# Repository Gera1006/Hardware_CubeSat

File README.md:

# Hardware_CubeSat
Aquí se encuentran los archivos creados para mantener un manejo más práctico de los elementos utilizados en el diseño del hardware

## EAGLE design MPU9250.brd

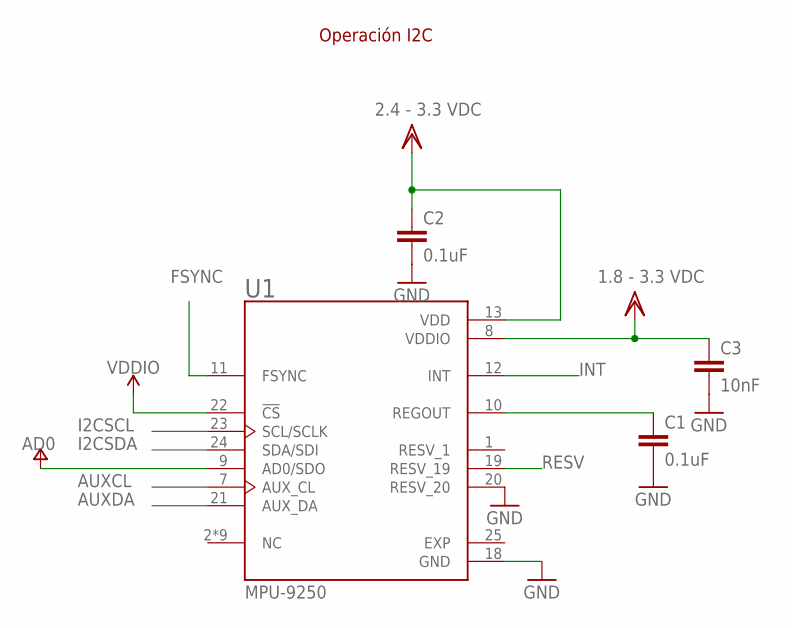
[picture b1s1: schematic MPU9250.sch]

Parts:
C1, C2: 0.1uF; 1206
C3: 10nF; 1206
U1: MPU-9250; QFN40P300X300X105-25N

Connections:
FSYNC: U1.11 (FSYNC)
GND: C1.2, C2.2, C3.2, U1.18 (GND), U1.20 (RESV_20)
INT: U1.12 (INT)
unnamed: C1.1, U1.10 (REGOUT)
RESV: U1.19 (RESV_19)
RESV_1: U1.1 (RESV_1)
V+: U1.9 (AD0/SDO)
VDD: C2.1, C3.1, U1.8 (VDDIO), U1.13 (VDD)
VDDIO: U1.22 (!CS)

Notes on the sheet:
Operación I2C

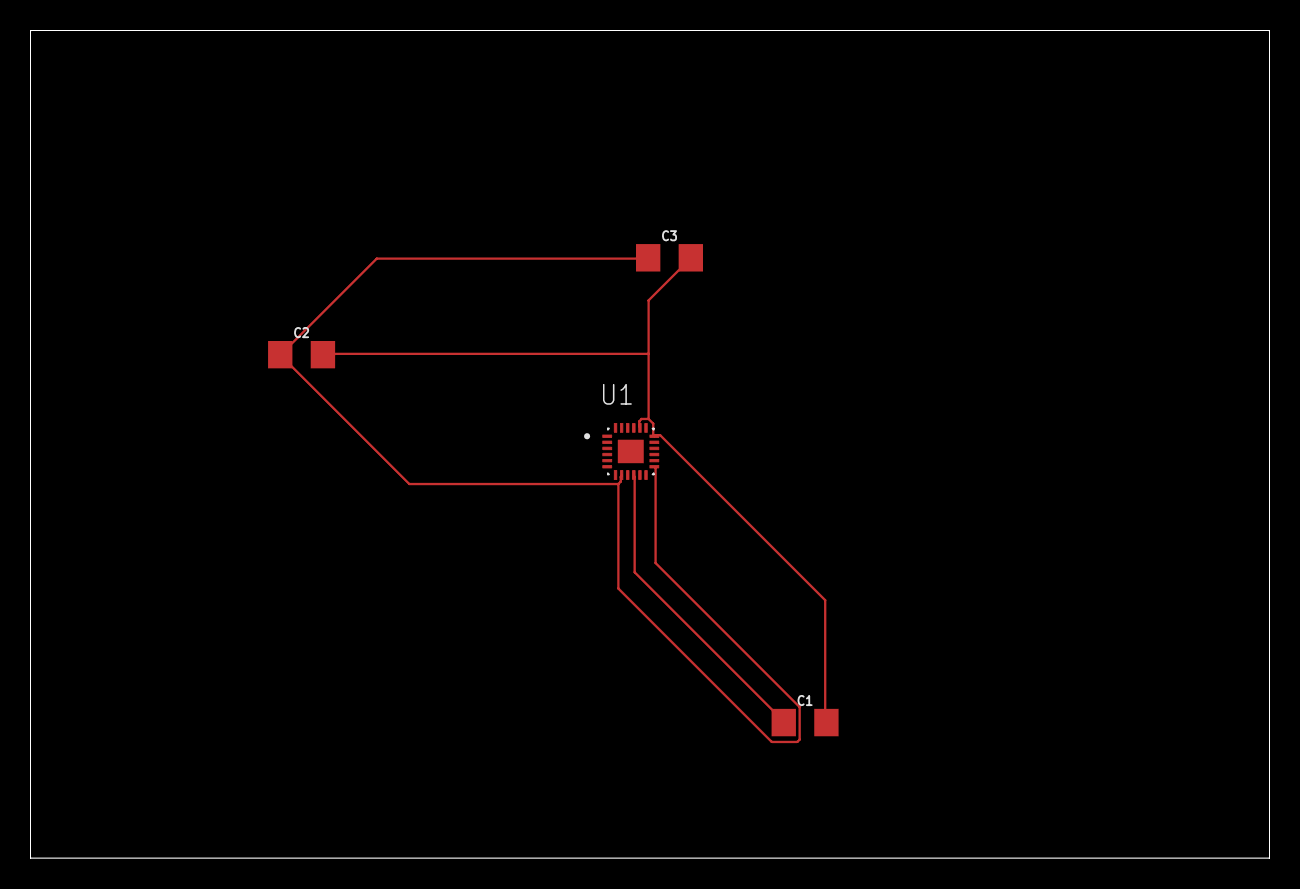
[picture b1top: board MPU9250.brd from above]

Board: 2 copper layers, 81.3 x 54.3 mm, 4 parts (0 on the bottom side), 3 nets.

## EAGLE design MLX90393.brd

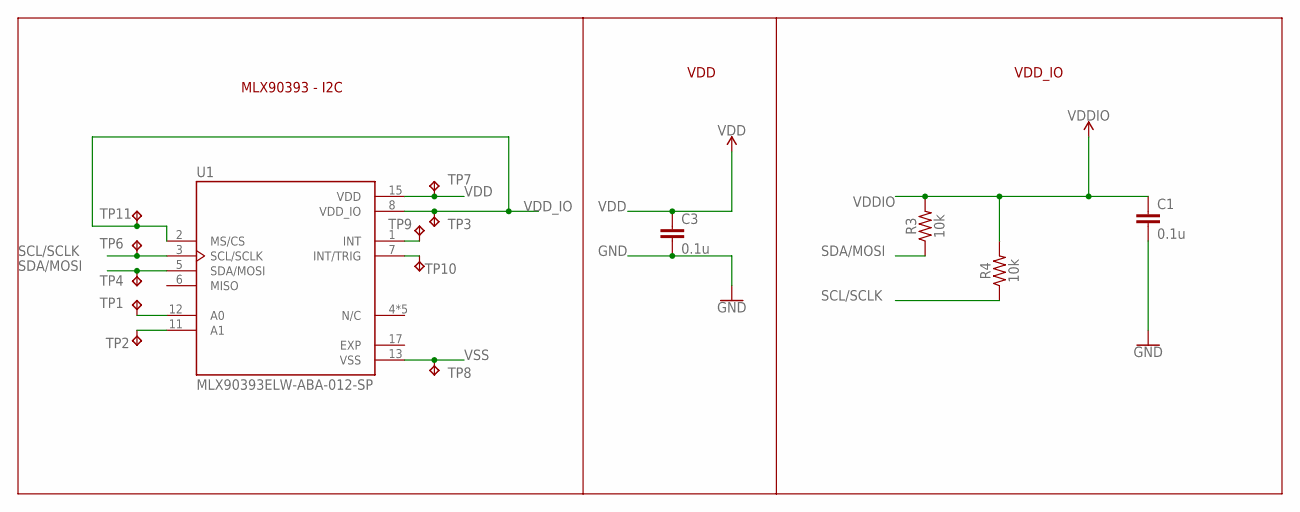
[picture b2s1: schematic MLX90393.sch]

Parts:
C1, C3: 0.1u; 1206
R3, R4: 10k; 1206
TP1, TP2, TP3, TP4, TP6, TP7, TP8, TP9, TP10, TP11: TPB1,27; B1,27
U1: MLX90393ELW-ABA-012-SP; QFN50P300X300X100-17N

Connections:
GND: C1.2, C3.2
unnamed: TP1.TP, U1.12 (A0)
unnamed: TP2.TP, U1.11 (A1)
unnamed: TP9.TP, U1.1 (INT)
unnamed: TP10.TP, U1.7 (INT/TRIG)
SCL/SCLK: R4.1, TP6.TP, U1.3 (SCL/SCLK)
SDA/MOSI: R3.1, TP4.TP, U1.5 (SDA/MOSI)
VDD: C3.1, TP7.TP, U1.15 (VDD)
VDDIO: C1.1, R3.2, R4.2
VDD_IO: TP3.TP, TP11.TP, U1.2 (MS/CS), U1.8 (VDD_IO)
VSS: TP8.TP, U1.13 (VSS)

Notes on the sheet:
MLX90393 - I2C
VDD
VDD_IO

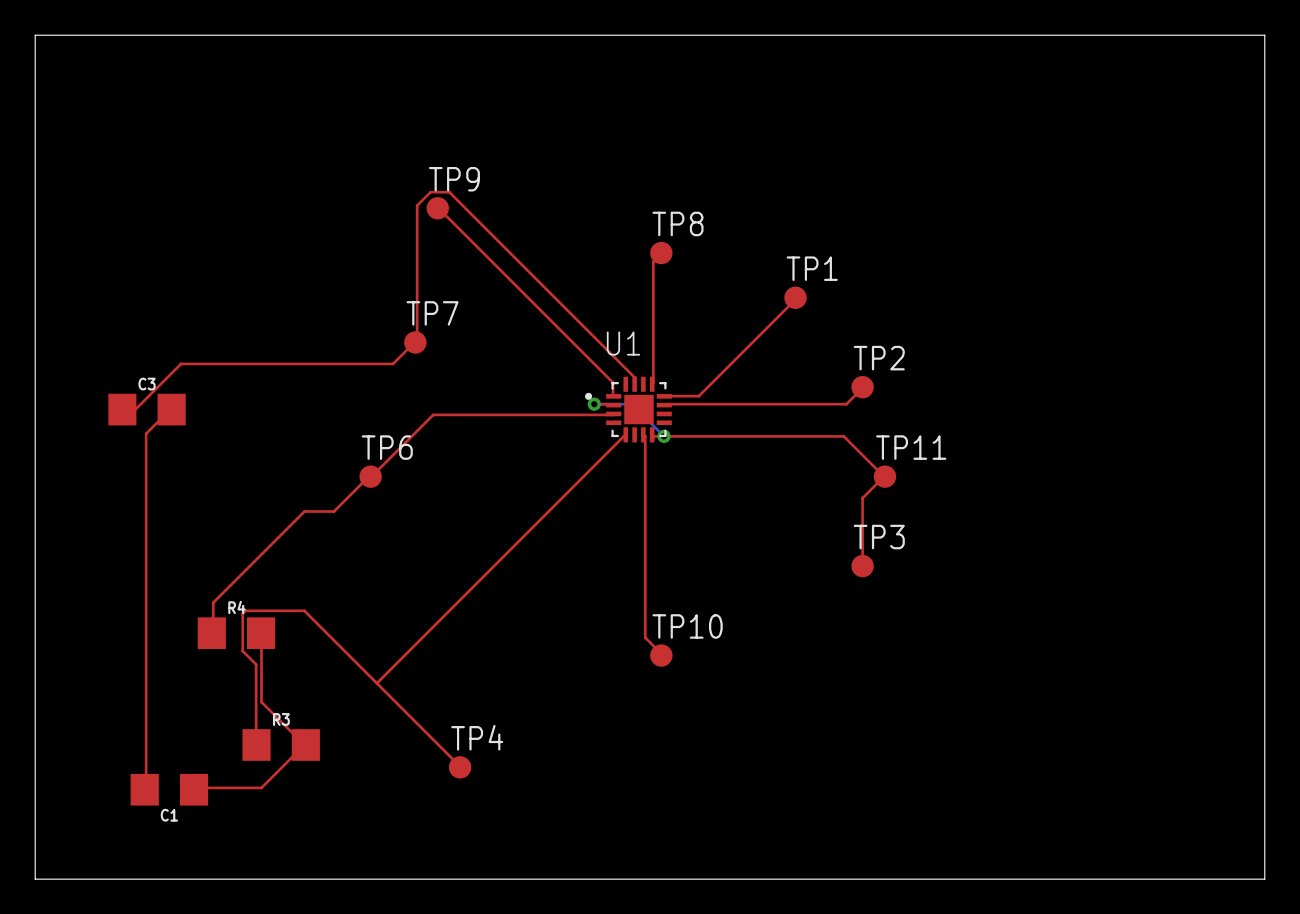
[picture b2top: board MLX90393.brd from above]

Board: 2 copper layers, 69.8 x 47.9 mm, 15 parts (0 on the bottom side), 11 nets.

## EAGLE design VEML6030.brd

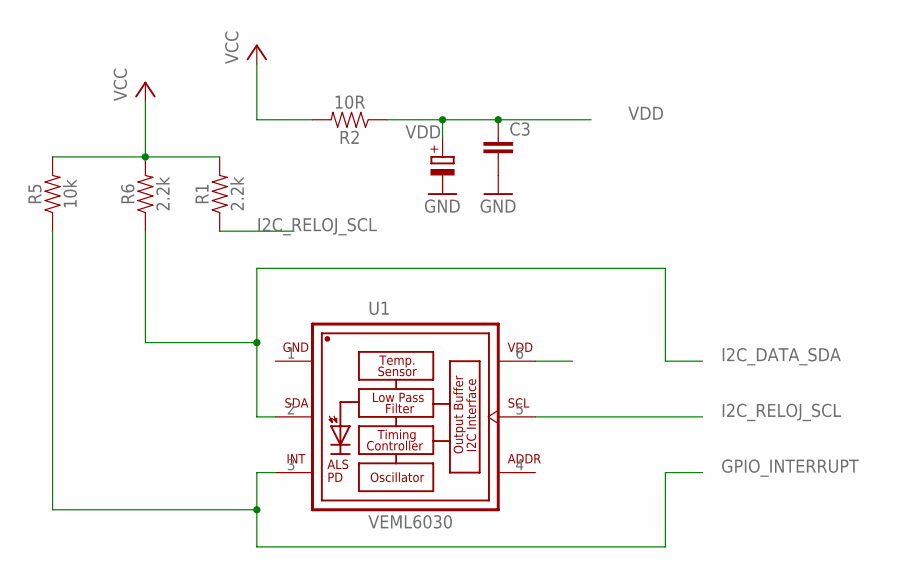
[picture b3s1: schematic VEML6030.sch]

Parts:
C3: CAP-1206; 1206
R1, R6: 2.2k; 1206
R2: 10R; 1206
R5: 10k; 1206
U1: VEML6030; VISHAY_VEML6030_2X2X0.87

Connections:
GND: C3.2, U1.1 (GND)
GPIO_INTERRUPT: R5.1, U1.3 (INT)
I2C_DATA_SDA: R6.1, U1.2 (SDA)
I2C_RELOJ_SCL: R1.1, U1.5 (SCL)
VCC: R1.2, R5.2, R6.2
VDD: C3.1, R2.1

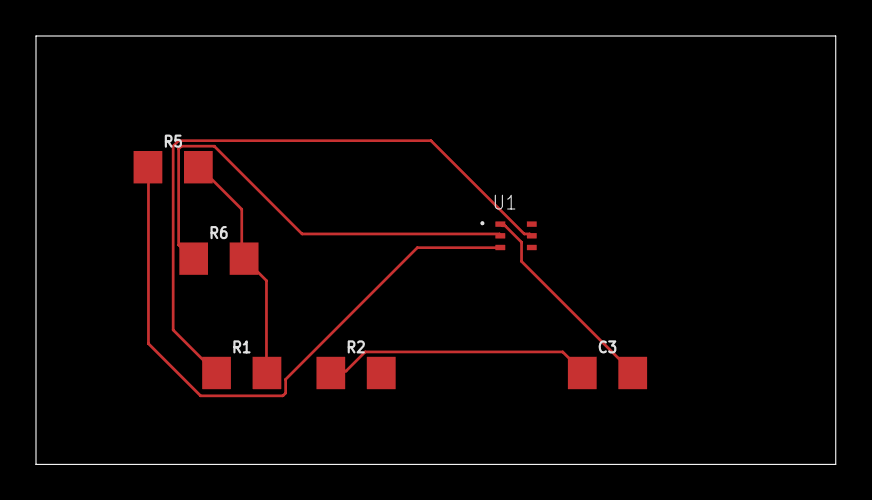
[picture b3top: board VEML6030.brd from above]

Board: 2 copper layers, 44.4 x 23.8 mm, 6 parts (0 on the bottom side), 6 nets.

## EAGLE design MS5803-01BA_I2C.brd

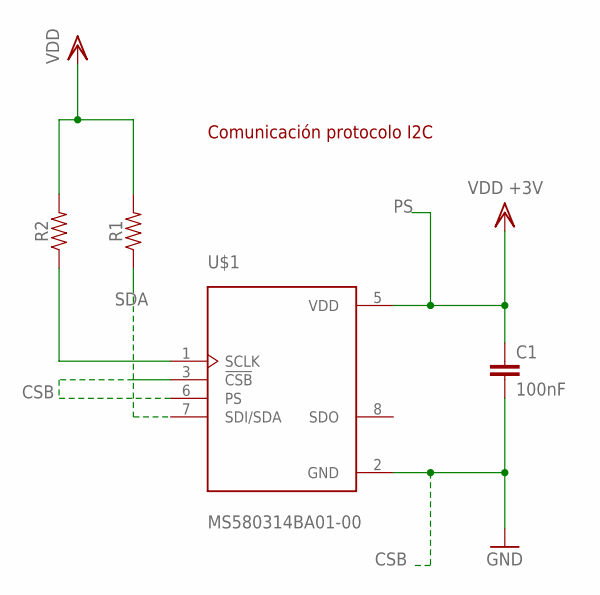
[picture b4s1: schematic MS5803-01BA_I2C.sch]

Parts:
C1: 100nF; 1206
R1, R2: 1206
U$1: MS580314BA01-00; XDCR_MS580314BA01-00

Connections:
CSB: C1.2, U$1.2 (GND), U$1.3 (!CSB), U$1.6 (PS)
PS: C1.1, U$1.5 (VDD)
SCLK: R2.1, U$1.1 (SCLK)
SDA: R1.1, U$1.7 (SDI/SDA)
VDD: R1.2, R2.2

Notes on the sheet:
Comunicación protocolo I2C

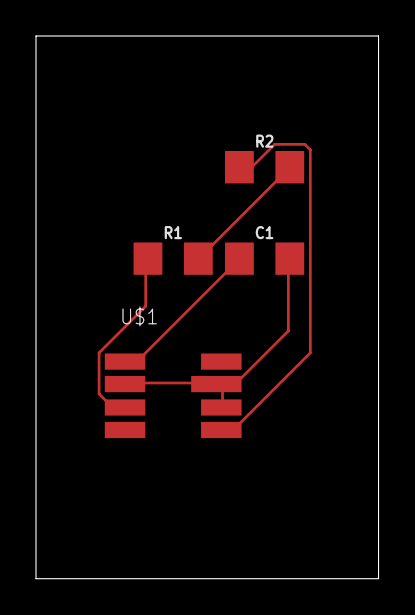
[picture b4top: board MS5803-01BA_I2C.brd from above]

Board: 2 copper layers, 19.0 x 30.1 mm, 4 parts (0 on the bottom side), 5 nets.

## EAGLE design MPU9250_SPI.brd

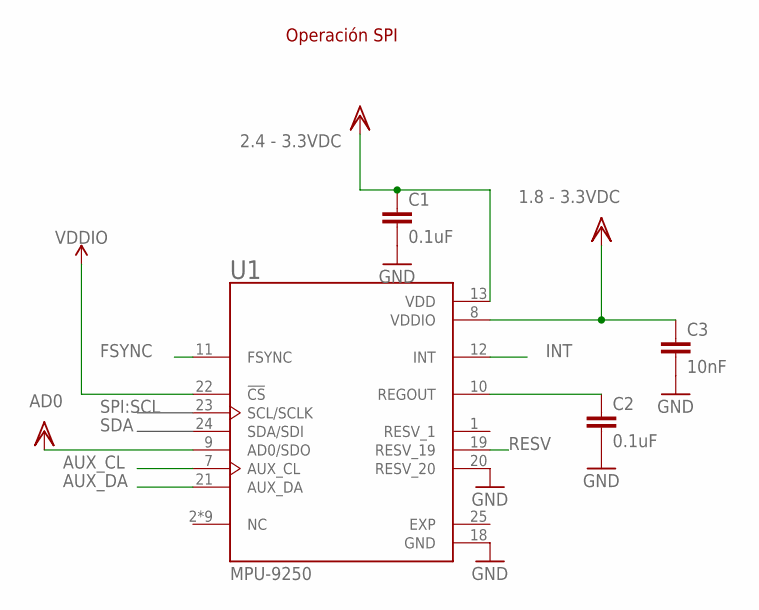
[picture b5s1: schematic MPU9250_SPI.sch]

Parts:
C1, C2: 0.1uF; 1206
C3: 10nF; 1206
U1: MPU-9250; QFN40P300X300X105-25N

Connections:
AUX_CL: U1.7 (AUX_CL)
AUX_DA: U1.21 (AUX_DA)
FSYNC: U1.11 (FSYNC)
GND: C1.2, C2.2, C3.2, U1.18 (GND), U1.20 (RESV_20)
INT: U1.12 (INT)
unnamed: C2.1, U1.10 (REGOUT)
RESV: U1.19 (RESV_19)
RESV_1: U1.1 (RESV_1)
VDD: C1.1, C3.1, U1.8 (VDDIO), U1.9 (AD0/SDO), U1.13 (VDD)
VDDIO: U1.22 (!CS)

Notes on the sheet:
Operación SPI

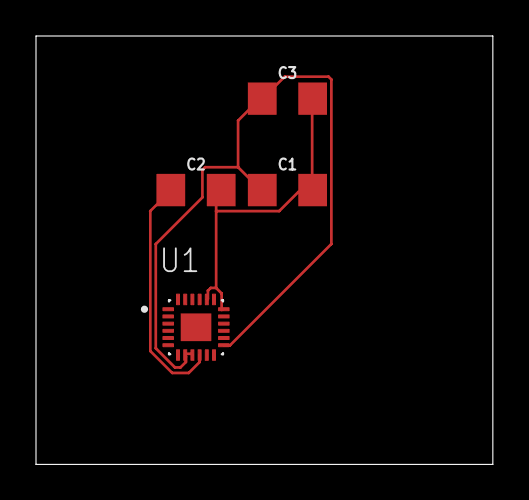
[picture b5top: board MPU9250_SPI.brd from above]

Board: 2 copper layers, 25.4 x 23.8 mm, 4 parts (0 on the bottom side), 3 nets.

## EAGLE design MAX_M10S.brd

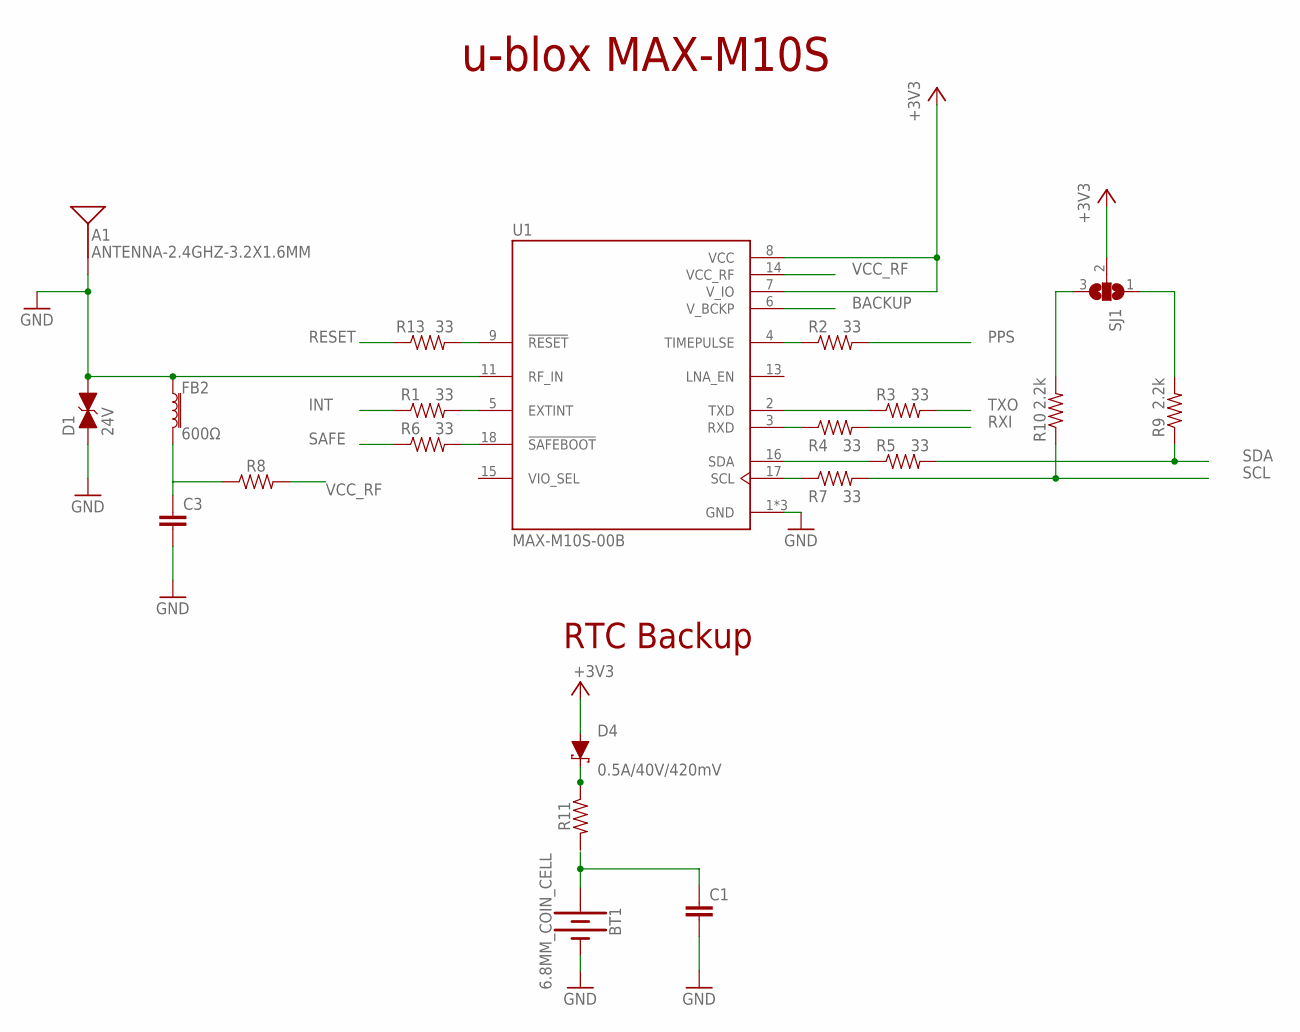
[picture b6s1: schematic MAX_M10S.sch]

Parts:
A1: ANTENNA-2.4GHZ-3.2X1.6MM; ANT-2.4GHZ-3.2X1.6X1.2MM
BT1: 6.8MM_COIN_CELL; BATTCON-6.8MM
C1, C3: CAP-1206; 1206
D1: 24V; 0603
D4: 0.5A/40V/420mV; SMA-DIODE
FB2: 600Ω; 0805
R1, R2, R3, R4, R5, R6, R7, R8, R11, R13: 33; 1206
R9, R10: 2.2k; 1206
SJ1: SJ2W; SJ_2
U1: MAX-M10S-00B; XCVR_MAX-M10S-00B

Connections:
+3V3: D4.A, SJ1.2
BACKUP: U1.6 (V_BCKP)
GND: BT1.-, C1.2, C3.2, D1.1 (A), U1.1 (GND), U1.10 (GND), U1.12 (GND)
INT: R1.1
unnamed: R2.1, U1.4 (TIMEPULSE)
unnamed: R3.1, U1.2 (TXD)
unnamed: R4.1, U1.3 (RXD)
unnamed: R5.1, U1.16 (SDA)
unnamed: R7.1, U1.17 (SCL)
unnamed: R13.2, U1.9 (!RESET)
unnamed: R1.2, U1.5 (EXTINT)
unnamed: R6.2, U1.18 (!SAFEBOOT)
unnamed: R10.2, SJ1.3
unnamed: R9.2, SJ1.1
unnamed: A1.FEED, D1.2 (C), FB2.1, U1.11 (RF_IN)
unnamed: C3.1, FB2.2, R8.1
unnamed: BT1.+, C1.1
unnamed: D4.C, R11.1
PPS: R2.2
RESET: R13.1
RXI: R4.2
SAFE: R6.1
SCL: R7.2, R10.1
SDA: R5.2, R9.1
SPPLY1: U1.7 (V_IO), U1.8 (VCC)
TXO: R3.2
VCC_RF: R8.2, U1.14 (VCC_RF)

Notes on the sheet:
u-blox MAX-M10S
RTC Backup

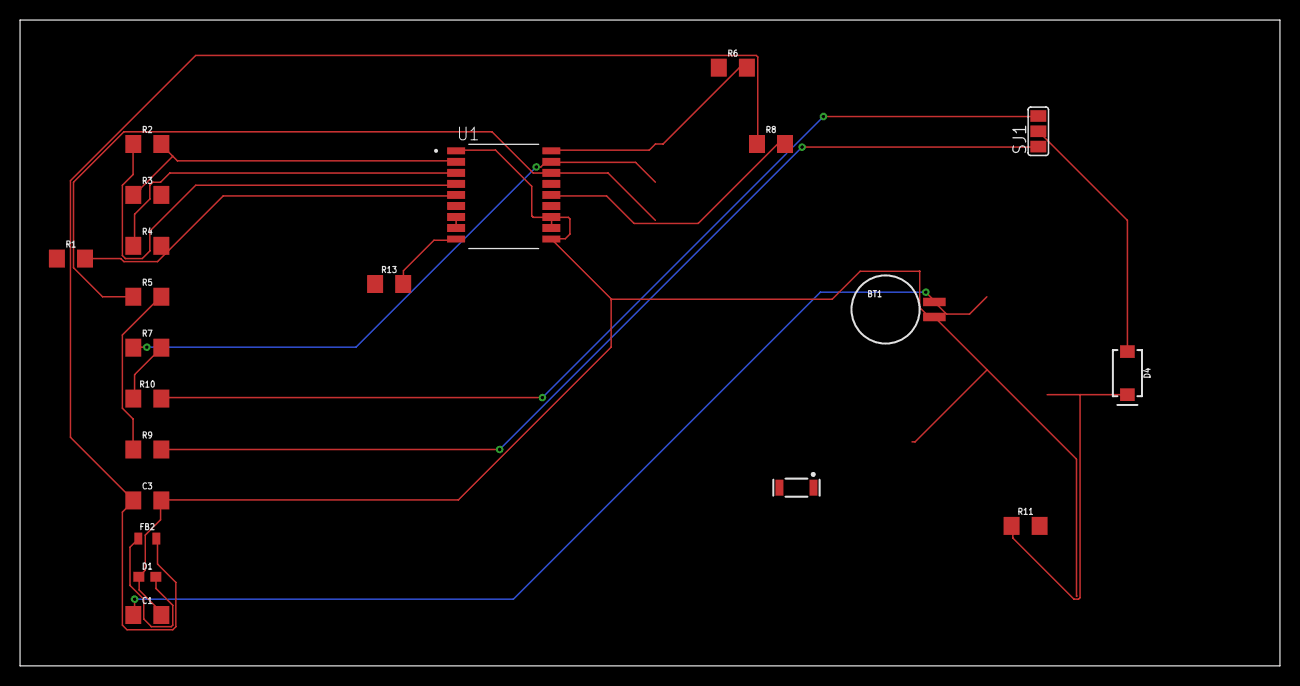
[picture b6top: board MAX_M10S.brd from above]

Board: 2 copper layers, 125.7 x 64.4 mm, 21 parts (0 on the bottom side), 20 nets.

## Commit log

2025-01-22 Add files via upload
    Archivos design block de los sensores.
2025-01-22 Add files via upload
    Archivos sch y brd de los sensores restantes
2025-01-29 Se añaden los archivos para KiCad
    Se toman los archivos de Eagle para pasarlos al formato compatible con KiCad

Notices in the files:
parts and their libraries:
SparkFun-Batteries: Licensing: Creative Commons ShareAlike 4.0 International - https://creativecommons.org/licenses/by-sa/4.0
